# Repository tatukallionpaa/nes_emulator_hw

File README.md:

Kicad project for hand held Nes emulator HW. Based on FK723M1-ZGT6 dev board. Software repo in https://github.com/tatukallionpaa/stm32_nes_emulator.

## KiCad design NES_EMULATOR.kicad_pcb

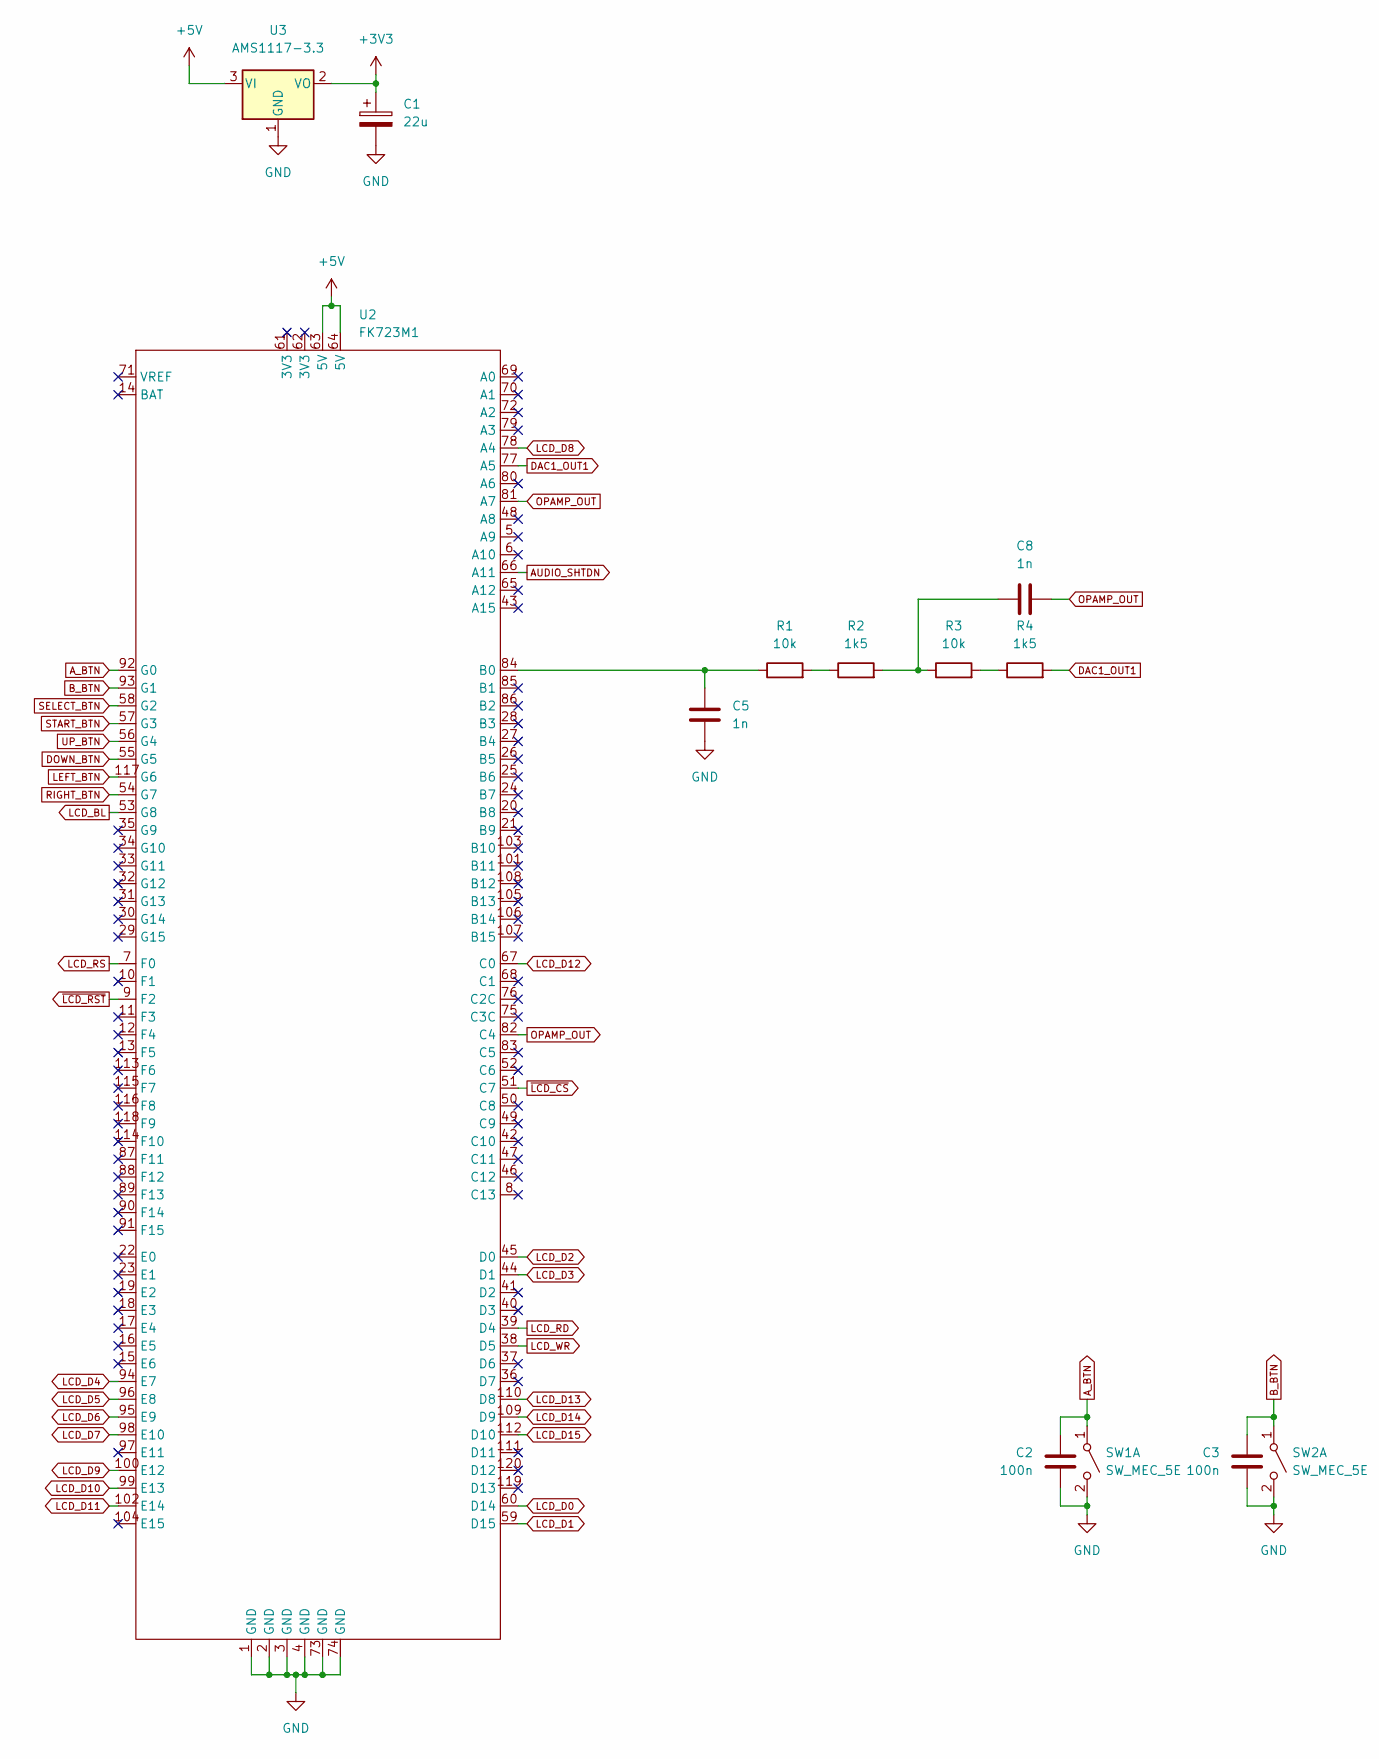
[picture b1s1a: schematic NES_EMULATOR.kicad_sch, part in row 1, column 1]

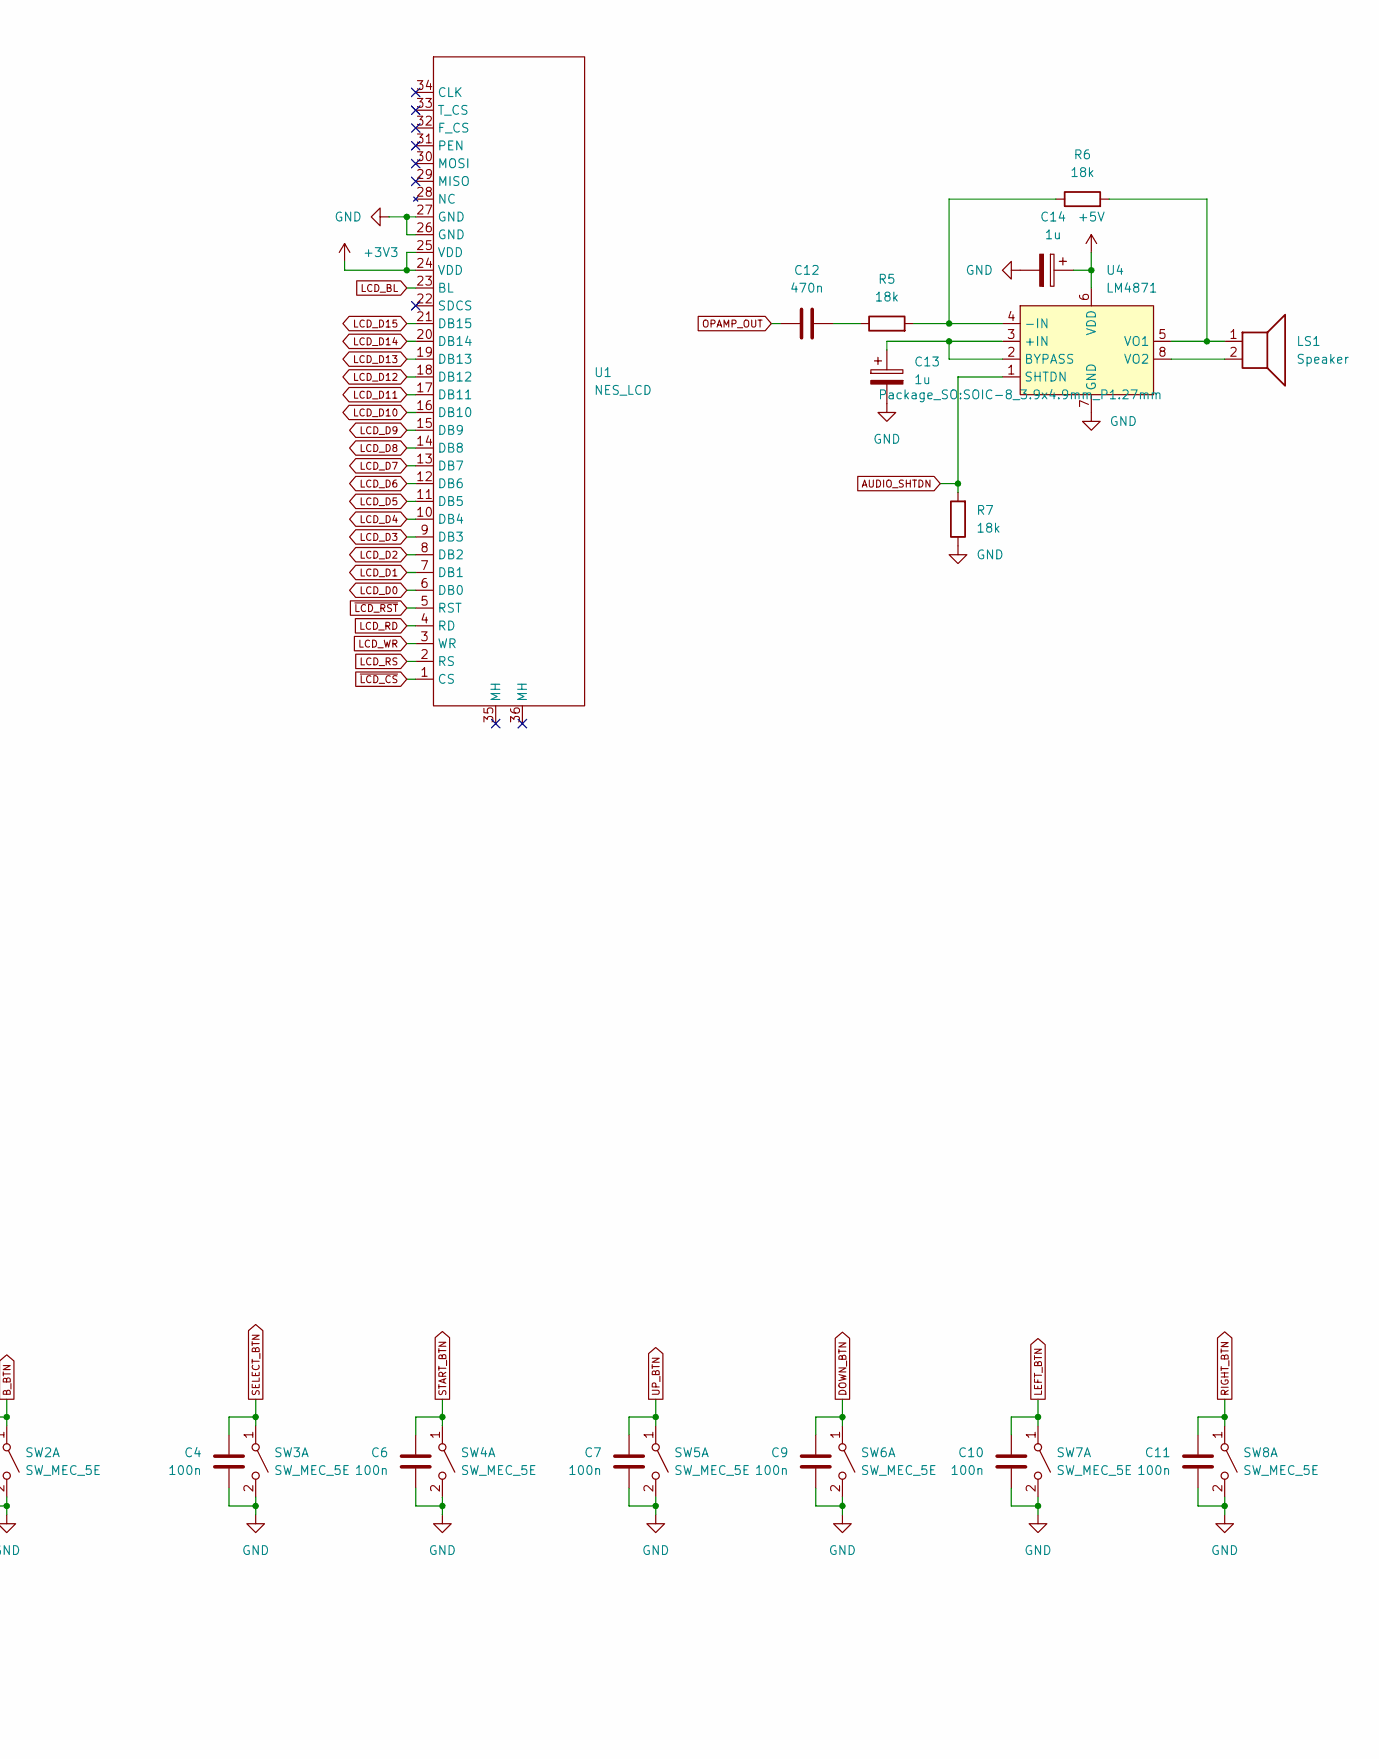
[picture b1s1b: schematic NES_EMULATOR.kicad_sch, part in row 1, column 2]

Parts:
C1: 22u; CP_Radial_D4.0mm_P2.00mm
C2, C3, C4, C6, C7, C9, C10, C11: 100n; C_0805_2012Metric_Pad1.18x1.45mm_HandSolder
C5, C8: 1n; C_Disc_D4.7mm_W2.5mm_P5.00mm
C12: 470n; C_Disc_D8.0mm_W5.0mm_P7.50mm
C13, C14: 1u; CP_Radial_D4.0mm_P2.00mm
LS1: Speaker; PCB_SPEAKER
R1, R3: 10k; R_0805_2012Metric_Pad1.20x1.40mm_HandSolder
R2, R4: 1k5; R_0805_2012Metric_Pad1.20x1.40mm_HandSolder
R5, R6, R7: 18k; R_0805_2012Metric_Pad1.20x1.40mm_HandSolder
SW1, SW2, SW5, SW6, SW7, SW8: SW_MEC_5E; SW_PUSH-12mm_Wuerth-430476085716
SW3, SW4: SW_MEC_5E; SW_SPST_PTS645
U1: NES_LCD
U2: FK723M1
U3: AMS1117-3.3; SOT-223-3_TabPin2
U4: LM4871; SOIC-8_3.9x4.9mm_P1.27mm

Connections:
+3V3: C1.1, U1.24 (VDD), U1.25 (VDD), U3.2 (VO)
+5V: C14.1, U2.63 (5V), U2.64 (5V), U3.3 (VI), U4.6 (VDD)
AUDIO_SHTDN: R7.2, U2.66 (A11), U4.1 (SHTDN)
A_BTN: C2.2, SW1.1 (A), U2.92 (G0)
B_BTN: C3.2, SW2.1 (A), U2.93 (G1)
DAC1_OUT1: R4.2, U2.77 (A5)
DOWN_BTN: C9.2, SW6.1 (A), U2.55 (G5)
GND: C1.2, C2.1, C3.1, C4.1, C5.1, C6.1, C7.1, C9.1, C10.1, C11.1, C13.2, C14.2, R7.1, SW1.2 (B), SW2.2 (B), SW3.2 (B), SW4.2 (B), SW5.2 (B), SW6.2 (B), SW7.2 (B), SW8.2 (B), U1.26 (GND), U1.27 (GND), U2.1 (GND), U2.2 (GND), U2.3 (GND), U2.4 (GND), U2.73 (GND), U2.74 (GND), U3.1 (GND), U4.7 (GND)
LCD_BL: U1.23 (BL), U2.53 (G8)
LCD_D0: U1.6 (DB0), U2.60 (D14)
LCD_D1: U1.7 (DB1), U2.59 (D15)
LCD_D2: U1.8 (DB2), U2.45 (D0)
LCD_D3: U1.9 (DB3), U2.44 (D1)
LCD_D4: U1.10 (DB4), U2.94 (E7)
LCD_D5: U1.11 (DB5), U2.96 (E8)
LCD_D6: U1.12 (DB6), U2.95 (E9)
LCD_D7: U1.13 (DB7), U2.98 (E10)
LCD_D8: U1.14 (DB8), U2.78 (A4)
LCD_D9: U1.15 (DB9), U2.100 (E12)
LCD_D10: U1.16 (DB10), U2.99 (E13)
LCD_D11: U1.17 (DB11), U2.102 (E14)
LCD_D12: U1.18 (DB12), U2.67 (C0)
LCD_D13: U1.19 (DB13), U2.110 (D8)
LCD_D14: U1.20 (DB14), U2.109 (D9)
LCD_D15: U1.21 (DB15), U2.112 (D10)
LCD_RD: U1.4 (RD), U2.39 (D4)
LCD_RS: U1.2 (RS), U2.7 (F0)
LCD_WR: U1.3 (WR), U2.38 (D5)
LEFT_BTN: C10.2, SW7.1 (A), U2.117 (G6)
unnamed: C8.2, R2.2, R3.1
unnamed: C12.1, R5.1
unnamed: R1.2, R2.1
unnamed: R3.2, R4.1
unnamed: C5.2, R1.1, U2.84 (B0)
unnamed: C13.1, U4.2 (BYPASS), U4.3 (+IN)
unnamed: R5.2, R6.1, U4.4 (-IN)
unnamed: LS1.1, R6.2, U4.5 (VO1)
unnamed: LS1.2, U4.8 (VO2)
OPAMP_OUT: C8.1, C12.2, U2.81 (A7), U2.82 (C4)
RIGHT_BTN: C11.2, SW8.1 (A), U2.54 (G7)
SELECT_BTN: C4.2, SW3.1 (A), U2.58 (G2)
START_BTN: C6.2, SW4.1 (A), U2.57 (G3)
UP_BTN: C7.2, SW5.1 (A), U2.56 (G4)
~LCD_CS: U1.1 (CS), U2.51 (C7)
~LCD_RST: U1.5 (RST), U2.9 (F2)

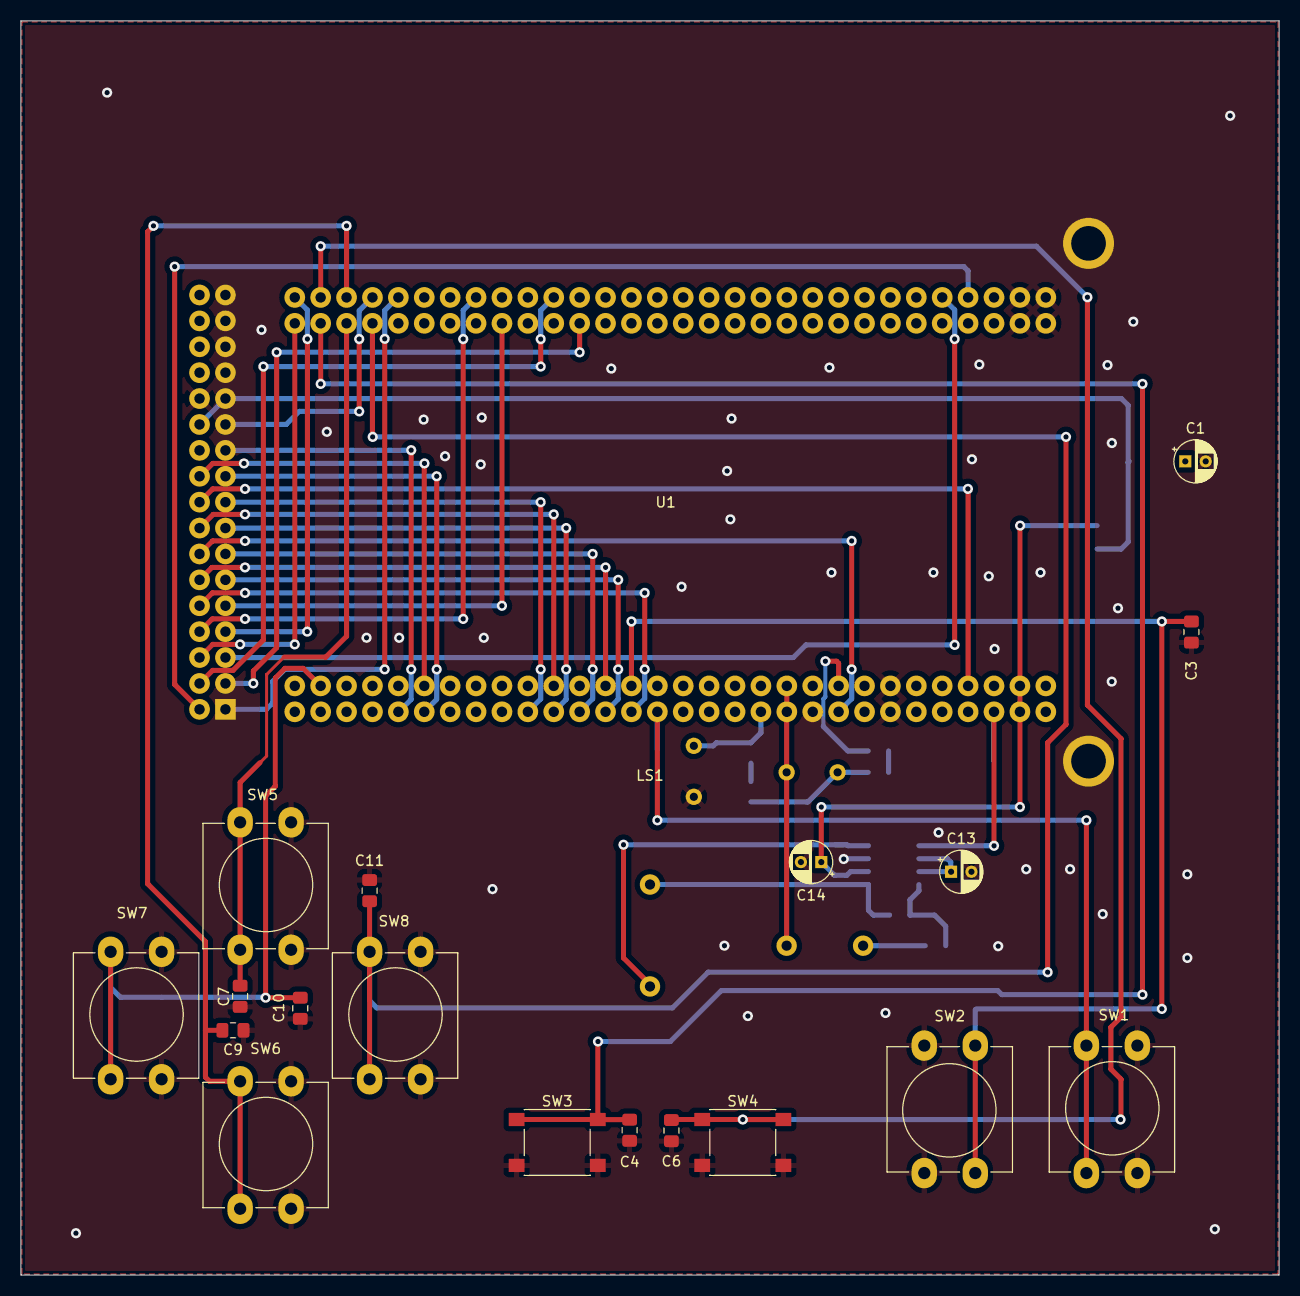
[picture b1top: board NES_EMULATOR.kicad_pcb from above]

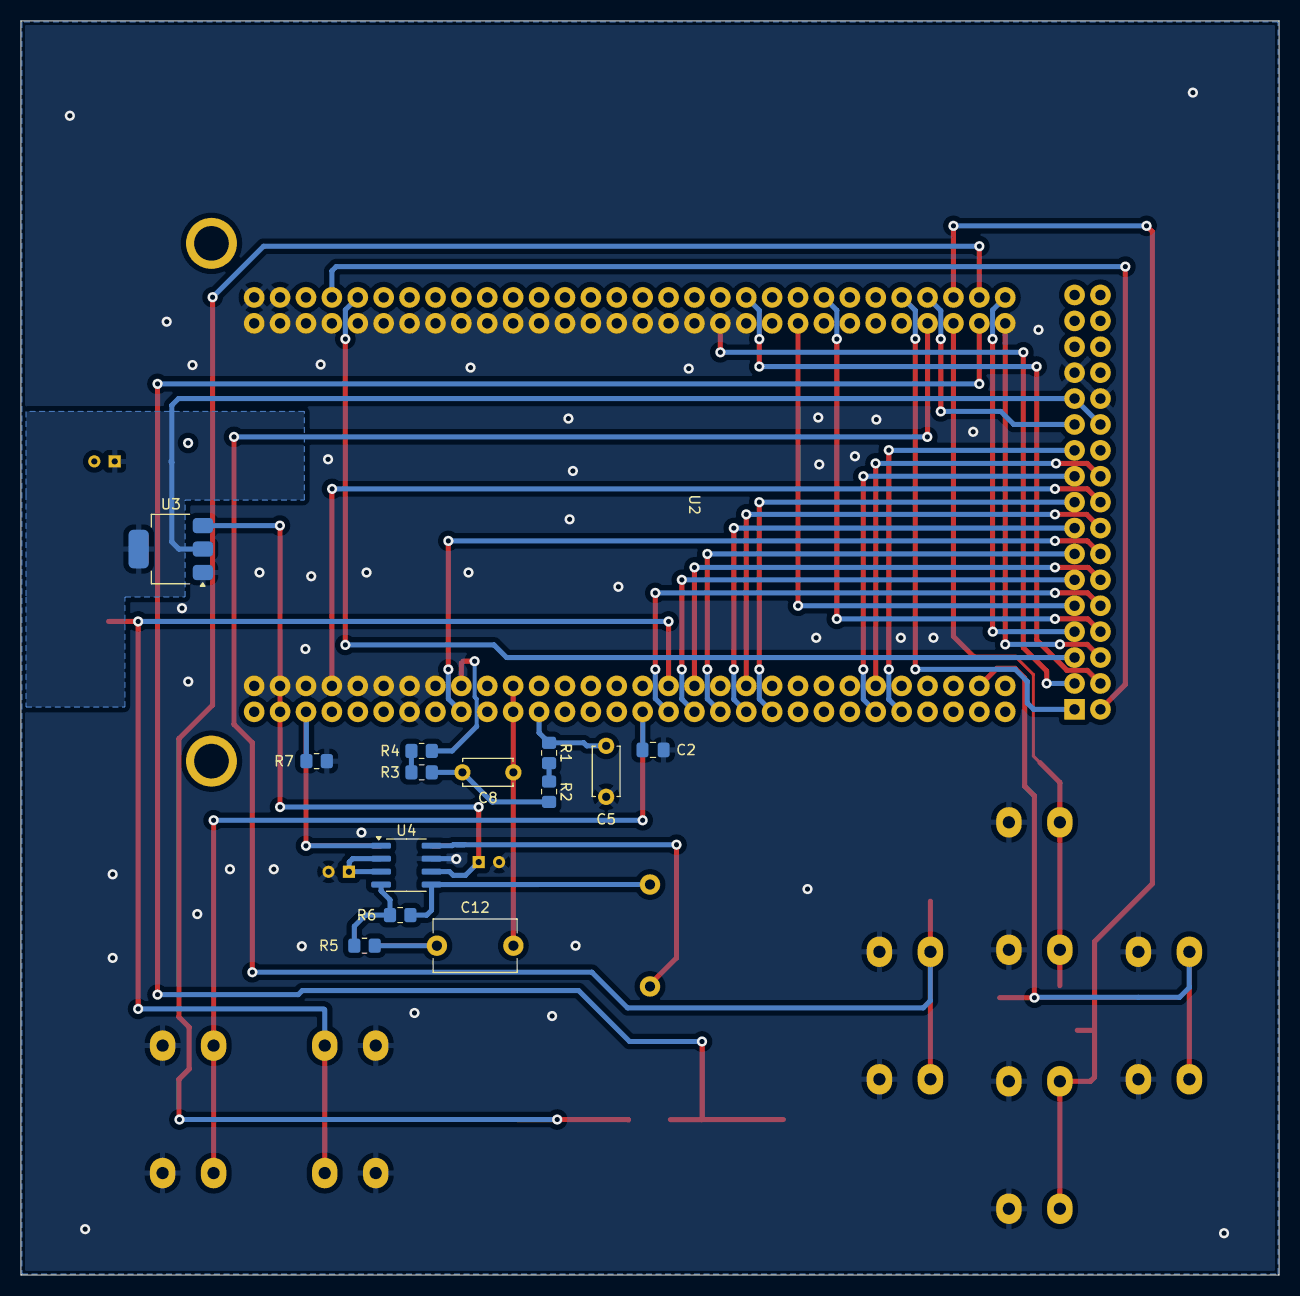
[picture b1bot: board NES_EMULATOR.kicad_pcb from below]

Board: 2 copper layers, 123.4 x 123.0 mm, 34 parts (14 on the bottom side), 45 nets.

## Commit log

2024-08-26 first functional version of nes emulator hw
2024-12-06 Fixed pcb design
